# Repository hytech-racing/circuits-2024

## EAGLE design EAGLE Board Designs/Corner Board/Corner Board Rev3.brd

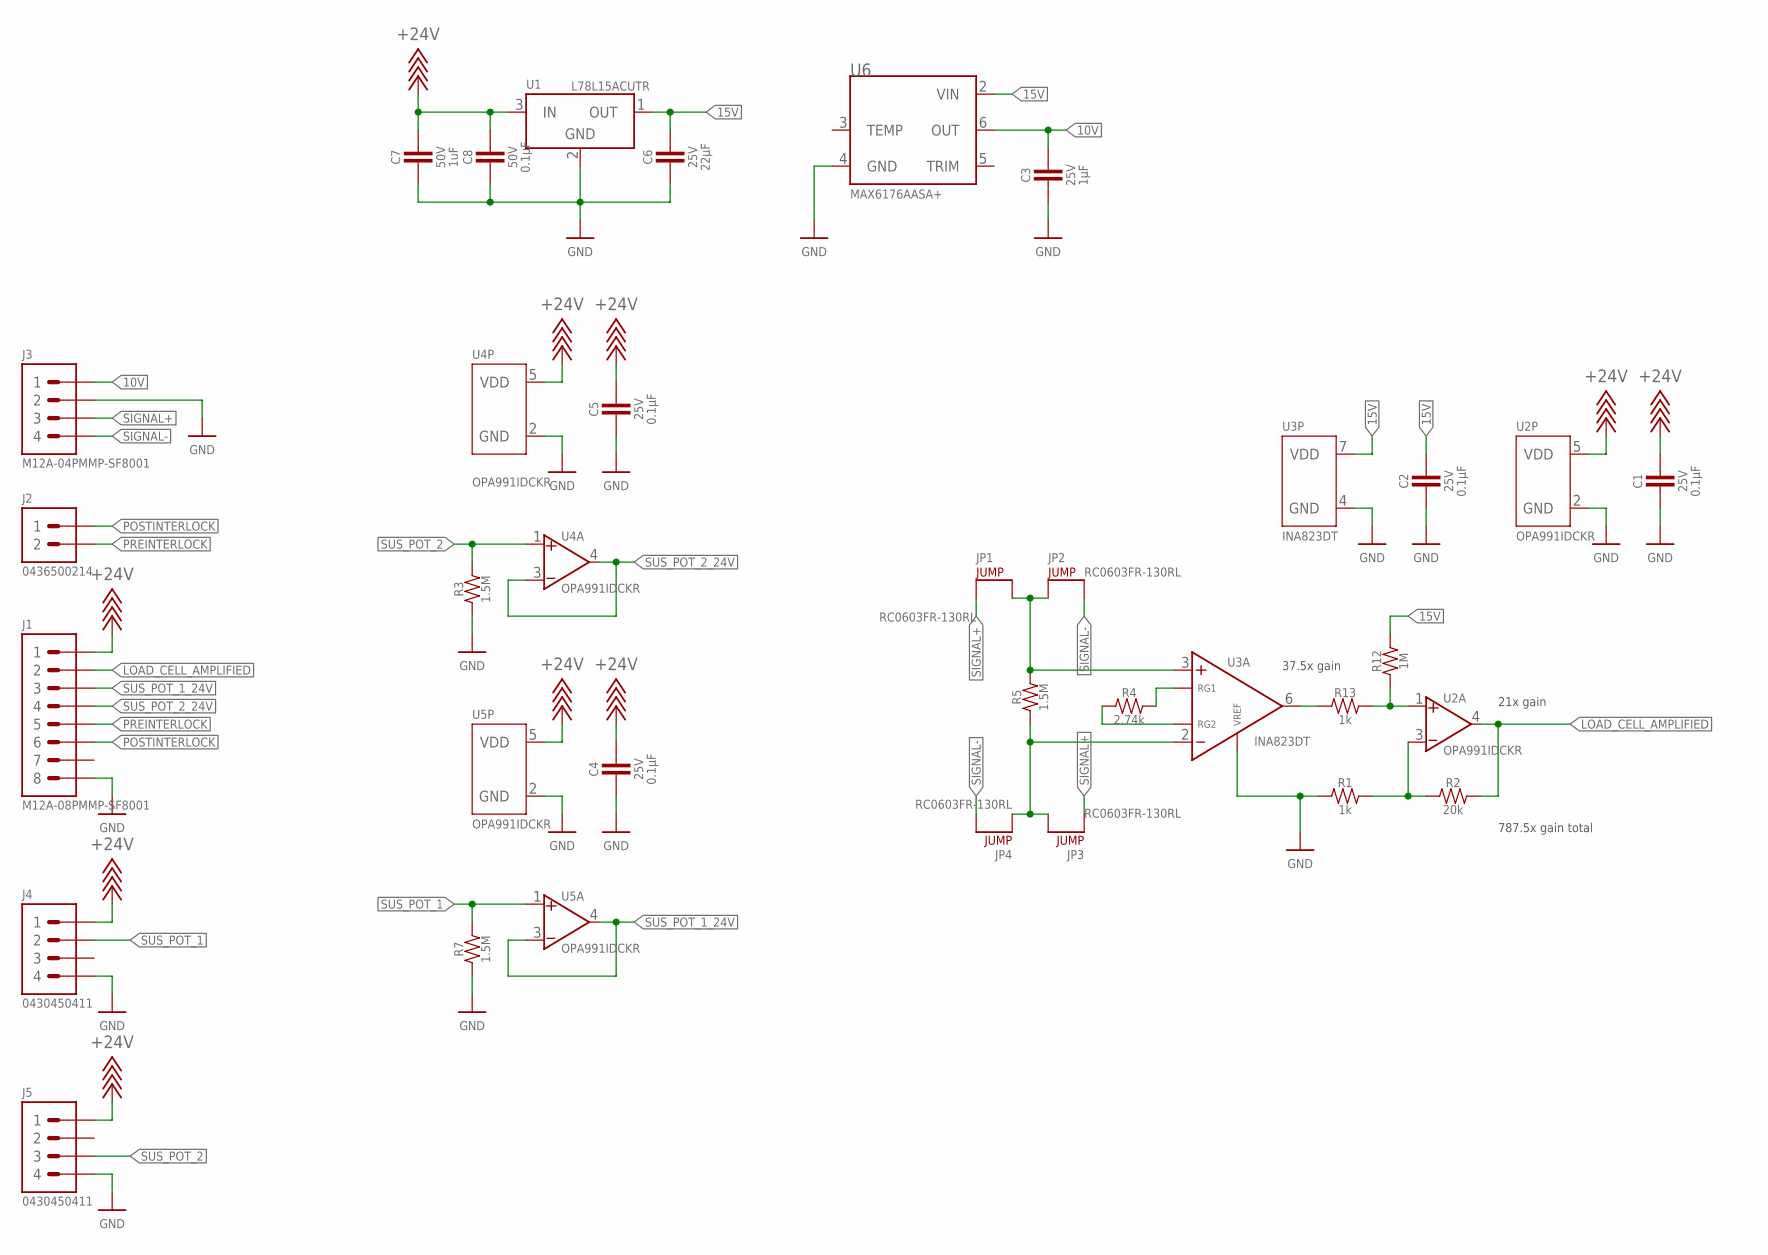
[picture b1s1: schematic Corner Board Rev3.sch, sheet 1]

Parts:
C1, C2, C4, C5: CAPACITOR_0603_25V_0.1UF; 0603-CAP
C3: CAPACITOR_0603_25V_1UF; 0603-CAP
C6: CAPACITOR_0805_25V_22UF; 0805-CAP
C7: CAPACITOR_0603_50V_1UF; 0603-CAP
C8: CAPACITOR_0603_50V_0.1UF; 0603-CAP
J1: CONNECTOR-8_AMPHENOL_M12A_08PMMP_; M12A-08PMMP
J2: CONNECTOR-2_MICROFIT_SMD_RIGHTANGLE_02_SINGLE_BLA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; MOLEX_MICROFIT_SMD_RIGHTANGLE_02_SINGLE
J3: CONNECTOR-4_AMPHENOL_M12A_04PMMP_; M12A-04PMMP
J4, J5: CONNECTOR-4_μF_S_RA_; MOLEX_MICROFIT_SMD_RIGHTANGLE_04_DUAL
JP1, JP2, JP3, JP4: JUMPER_0603_; 0603-RES
R1, R13: RESISTOR_0603_1K; 0603-RES
R2: RESISTOR_0603_20K; 0603-RES
R3, R5, R7: RESISTOR_0603_1.5M; 0603-RES
R4: RESISTOR_0603_2.74K; 0603-RES
R12: RESISTOR_0603_1M; 0603-RES
U1: VOLTAGE_REGULATOR_SOT-89REVERSE_; SOT-89
U2, U4, U5: OPAMP_1_CHANNEL_OPA991; SC-70-5
U3: INA823DT; SOIC-08(NARROW,0.15")
U6: VOLTAGE_REFERENCE_SOIC-8_10V; SOIC-08(NARROW,0.15")

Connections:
10V: C3.1, J3.1, U6.6 (OUT)
15V: C2.1, C6.1, R12.2, U1.1 (OUT), U3.7 (VDD), U6.2 (VIN)
+24V: C1.1, C4.1, C5.1, C7.1, C8.1, J1.1, J4.1, J5.1, U1.3 (IN), U2.5 (VDD), U4.5 (VDD), U5.5 (VDD)
GND: C1.2, C2.2, C3.2, C4.2, C5.2, C6.2, C7.2, C8.2, J1.8, J3.2, J4.4, J5.4, R1.1, R3.1, R7.1, U1.2 (GND), U2.2 (GND), U3.4 (GND), U3.5 (VREF), U4.2 (GND), U5.2 (GND), U6.4 (GND)
LOAD_CELL_AMPLIFIED: J1.2, R2.2, U2.4 (VOUT)
unnamed: R1.2, R2.1, U2.3 (VIN-)
unnamed: R4.2, U3.1 (RG1)
unnamed: R13.1, U3.6 (VOUT)
unnamed: R4.1, U3.8 (RG2)
unnamed: R12.1, R13.2, U2.1 (VIN+)
unnamed: JP3.2, JP4.1, R5.1, U3.2 (VIN-)
unnamed: JP1.2, JP2.1, R5.2, U3.3 (VIN+)
POSTINTERLOCK: J1.6, J2.1
PREINTERLOCK: J1.5, J2.2
SIGNAL+: J3.3, JP1.1, JP3.1
SIGNAL-: J3.4, JP2.2, JP4.2
SUS_POT_1: J4.2, R7.2, U5.1 (VIN+)
SUS_POT_1_24V: J1.3, U5.3 (VIN-), U5.4 (VOUT)
SUS_POT_2: J5.3, R3.2, U4.1 (VIN+)
SUS_POT_2_24V: J1.4, U4.3 (VIN-), U4.4 (VOUT)

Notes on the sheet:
37.5x gain
21x gain
787.5x gain total

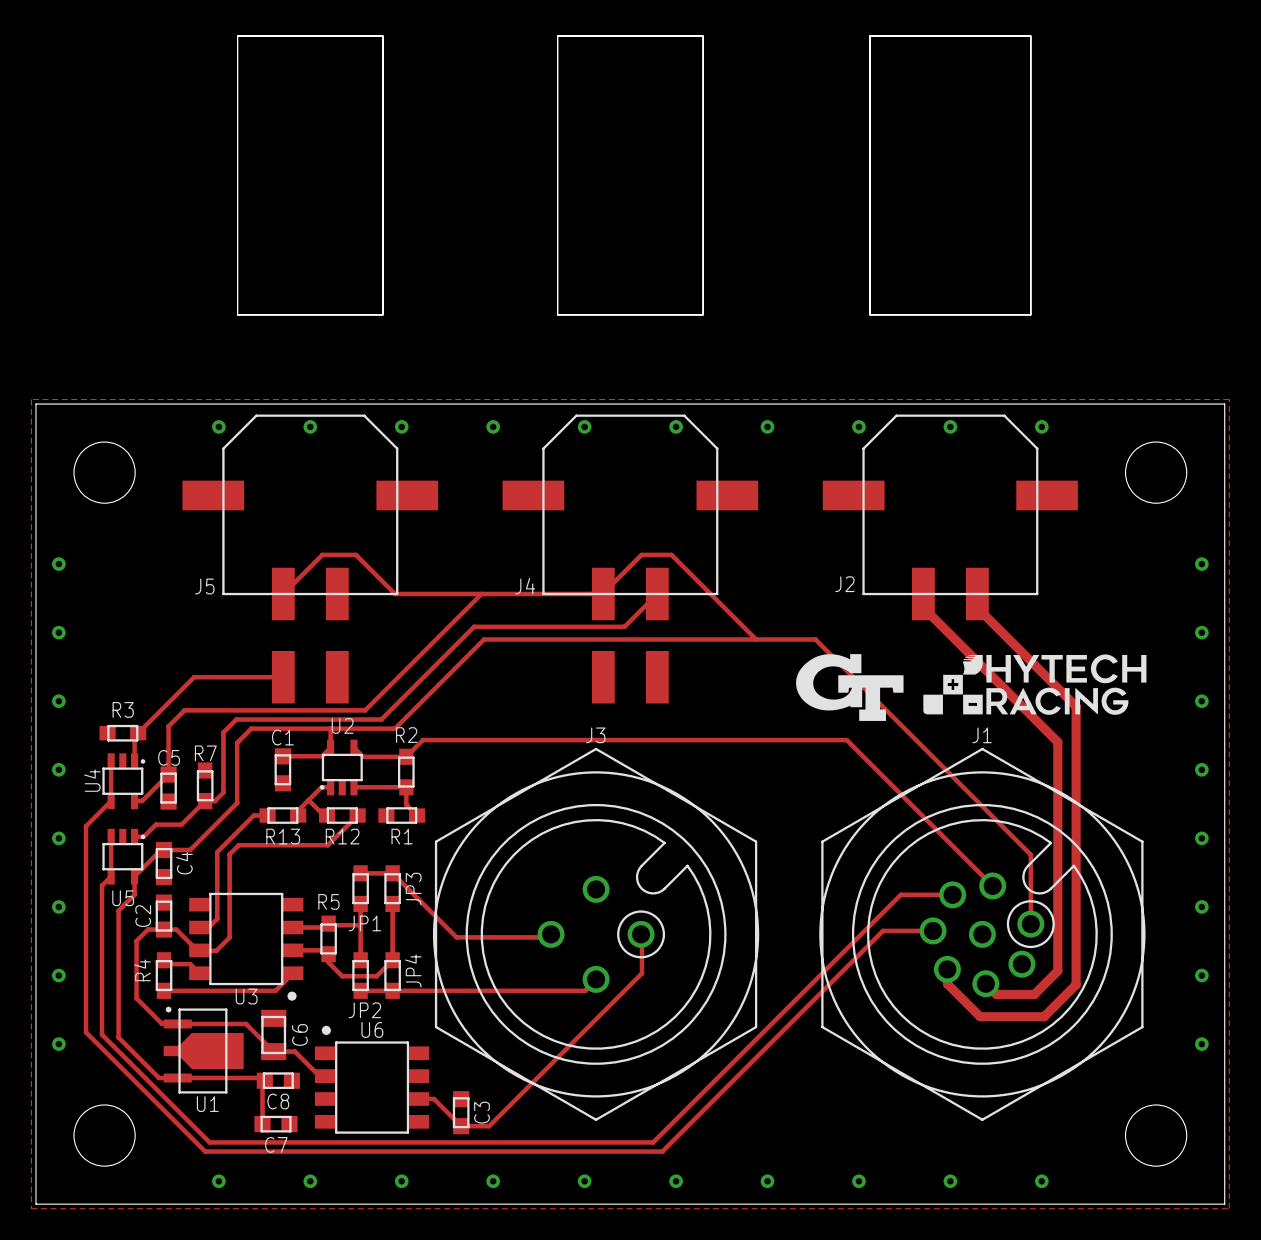
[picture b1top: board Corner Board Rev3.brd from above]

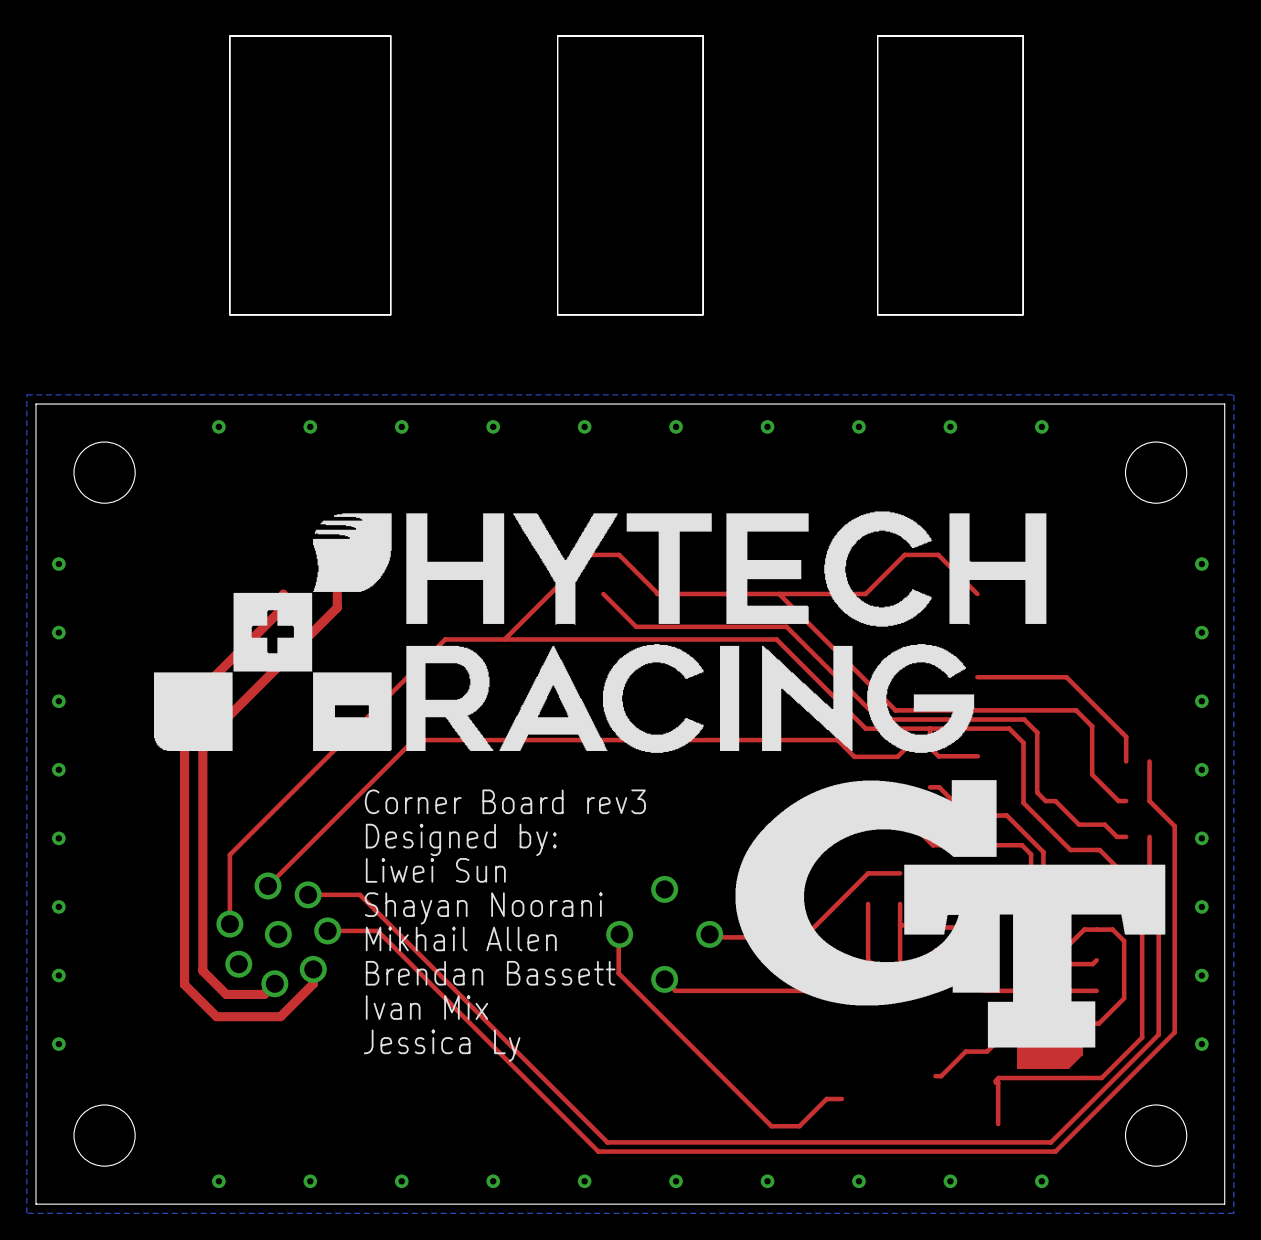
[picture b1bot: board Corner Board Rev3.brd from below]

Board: 2 copper layers, 66.0 x 44.5 mm, 39 parts (2 on the bottom side), 20 nets.

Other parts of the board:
U$6: LOGO_HYTECH_LARGE
U$7, U$8, U$9, U$10: MOUNTING_M3
U$14: LOGO_GT_SMALL
U$15: LOGO_GT_LARGE
U$19: LOGO_HYTECH_SMALL

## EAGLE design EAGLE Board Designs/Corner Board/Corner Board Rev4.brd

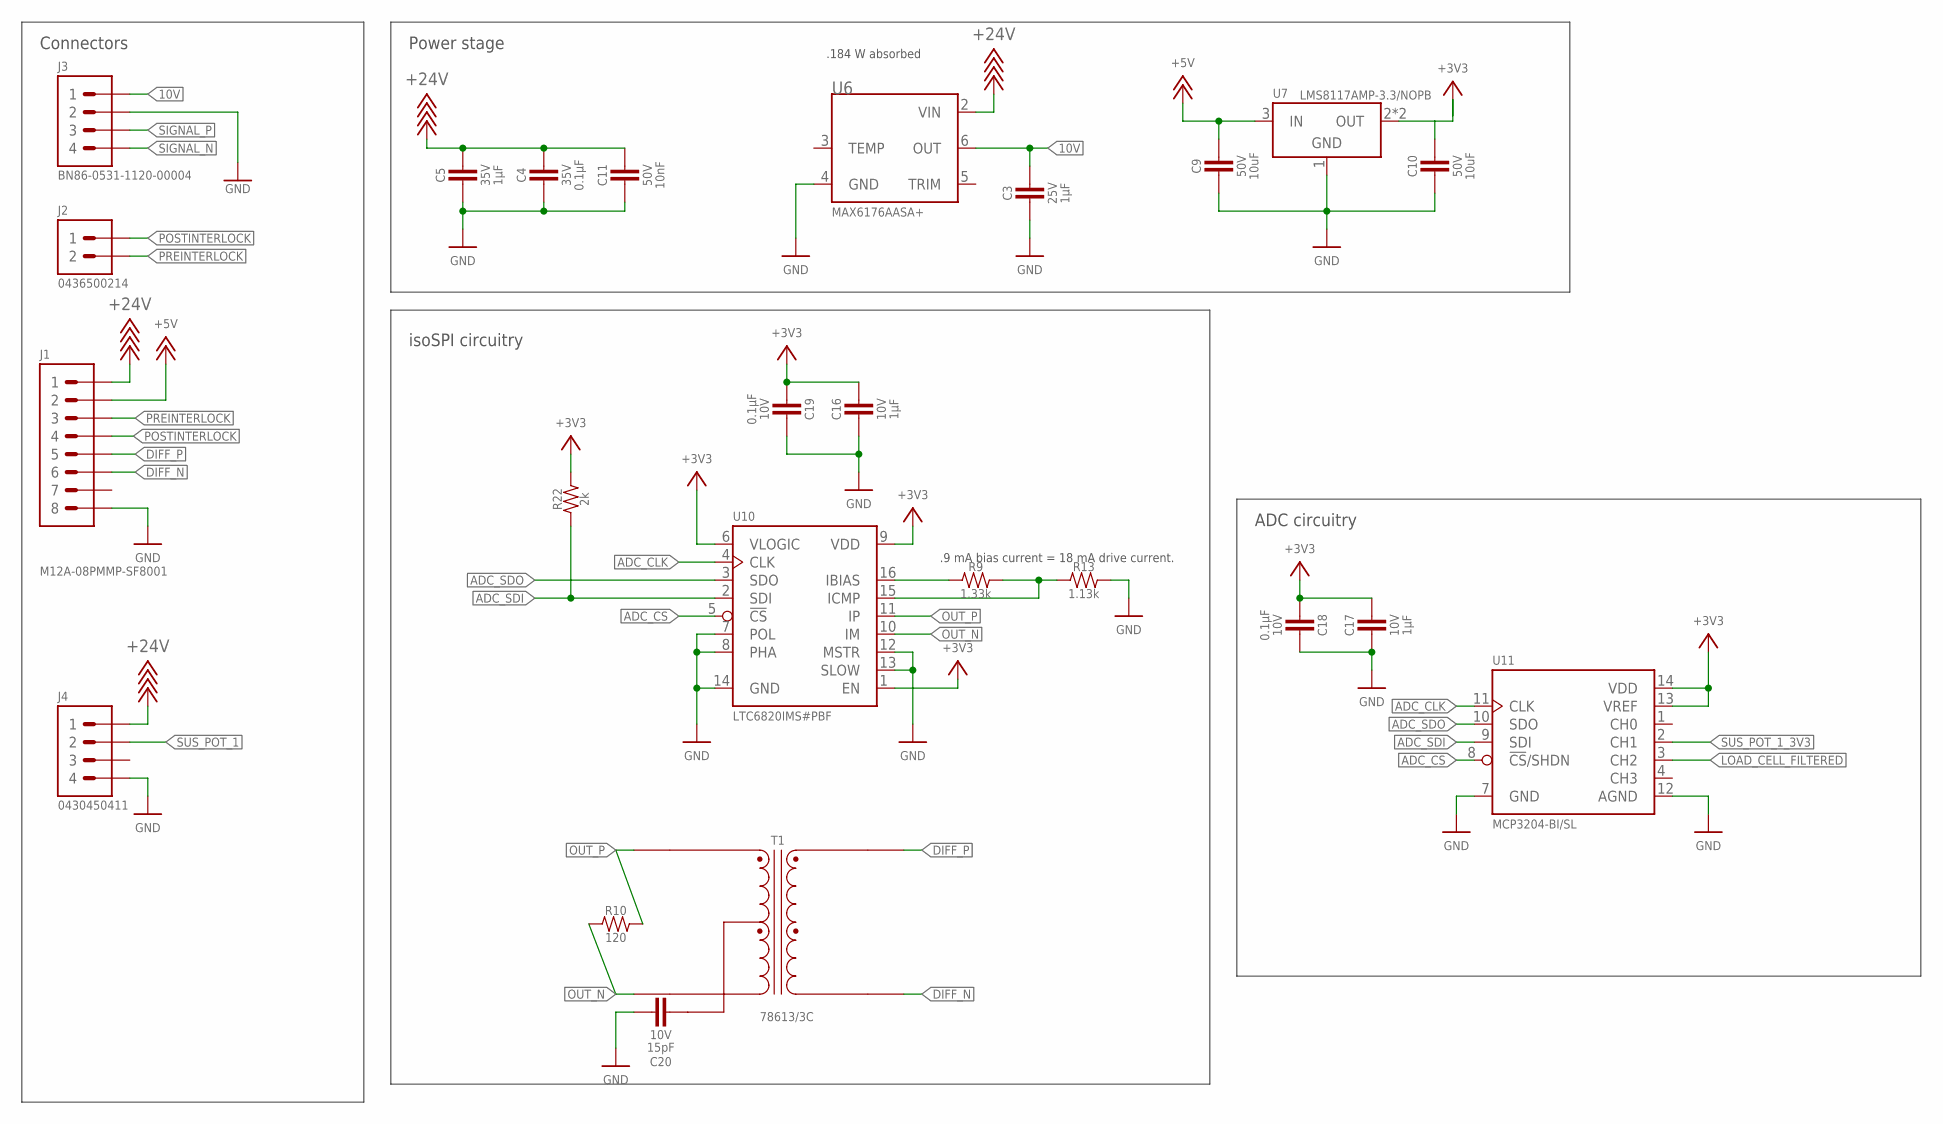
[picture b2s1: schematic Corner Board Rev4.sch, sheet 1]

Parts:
C3: CAPACITOR_0603_25V_1UF; 0603-CAP
C4: CAPACITOR_0603_35V_0.1UF; 0603-CAP
C5: CAPACITOR_0603_35V_1UF; 0603-CAP
C9, C10: CAPACITOR_0805_50V_10UF; 0805-CAP
C11: CAPACITOR_0603_50V_10NF; 0603-CAP
C16, C17: CAPACITOR_0603_10V_1UF; 0603-CAP
C18, C19: CAPACITOR_0603_10V_0.1UF; 0603-CAP
C20: CAPACITOR_0603_10V_15PF; 0603-CAP
J1: CONNECTOR-8_AMPHENOL_M12A_08PMMP_; M12A-08PMMP
J2: CONNECTOR-2_MICROFIT_SMD_RIGHTANGLE_02_SINGLE_BLA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; MOLEX_MICROFIT_SMD_RIGHTANGLE_02_SINGLE
J3: BINDER-M12-A_4_PIN; BINDER-86-0531-1120-00004M12
J4: CONNECTOR-4_μF_S_RA_; MOLEX_MICROFIT_SMD_RIGHTANGLE_04_DUAL
R9: RESISTOR_0603_1.33K; 0603-RES
R10: RESISTOR_0603_120; 0603-RES
R13: RESISTOR_0603_1.13K; 0603-RES
R22: RESISTOR_0603_2K; 0603-RES
T1: 78613/3C_78613/3C_AIRGAP; 78613/3C_AIRGAP
U6: VOLTAGE_REFERENCE_SOIC-8_10V; SOIC-08(NARROW,0.15")
U7: VOLTAGE_REGULATOR_SOT-223_3.3V; SOT-223
U10: LTC6820; MSOP-16
U11: MCP3204; SOIC-14

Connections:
10V: C3.1, J3.1, U6.6 (OUT)
+3V3: C10.1, C16.1, C17.1, C18.2, C19.2, R22.2, U7.2 (OUT), U7.4 (OUT), U10.1 (EN), U10.6 (VLOGIC), U10.9 (VDD), U11.13 (VREF), U11.14 (VDD); also elsewhere on the board
+5V: C9.1, J1.2, U7.3 (IN)
+24V: C4.1, C5.1, C11.1, J1.1, J4.1, U6.2 (VIN); also elsewhere on the board
ADC_CLK: U10.4 (CLK), U11.11 (CLK)
ADC_CS: U10.5 (!CS), U11.8 (!CS!/SHDN)
ADC_SDI: R22.1, U10.2 (SDI), U11.9 (SDI)
ADC_SDO: U10.3 (SDO), U11.10 (SDO)
DIFF_N: J1.6, T1.4 (SEC_1)
DIFF_P: J1.5, T1.6 (SEC_2)
GND: C3.2, C4.2, C5.2, C9.2, C10.2, C11.2, C16.2, C17.2, C18.1, C19.1, C20.2, J1.8, J3.2, J4.4, R13.2, U6.4 (GND), U7.1 (GND), U10.7 (POL), U10.8 (PHA), U10.12 (MSTR), U10.13 (SLOW), U10.14 (GND), U11.7 (GND), U11.12 (AGND); also elsewhere on the board
LOAD_CELL_FILTERED: U11.3 (CH2); also elsewhere on the board
unnamed: C20.1, T1.2 (PRI_CENTER_TAP)
unnamed: R9.1, U10.16 (IBIAS)
unnamed: R9.2, R13.1, U10.15 (ICMP)
OUT_N: R10.1, T1.3 (PRI_2), U10.10 (IM)
OUT_P: R10.2, T1.1 (PRI_1), U10.11 (IP)
POSTINTERLOCK: J1.4, J2.1
PREINTERLOCK: J1.3, J2.2
SIGNAL_N: J3.4; also elsewhere on the board
SIGNAL_P: J3.3; also elsewhere on the board
SUS_POT_1: J4.2; also elsewhere on the board
SUS_POT_1_3V3: U11.2 (CH1); also elsewhere on the board

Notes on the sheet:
.9 mA bias current = 18 mA drive current.
.184 W absorbed
isoSPI circuitry
ADC circuitry
Power stage
Connectors

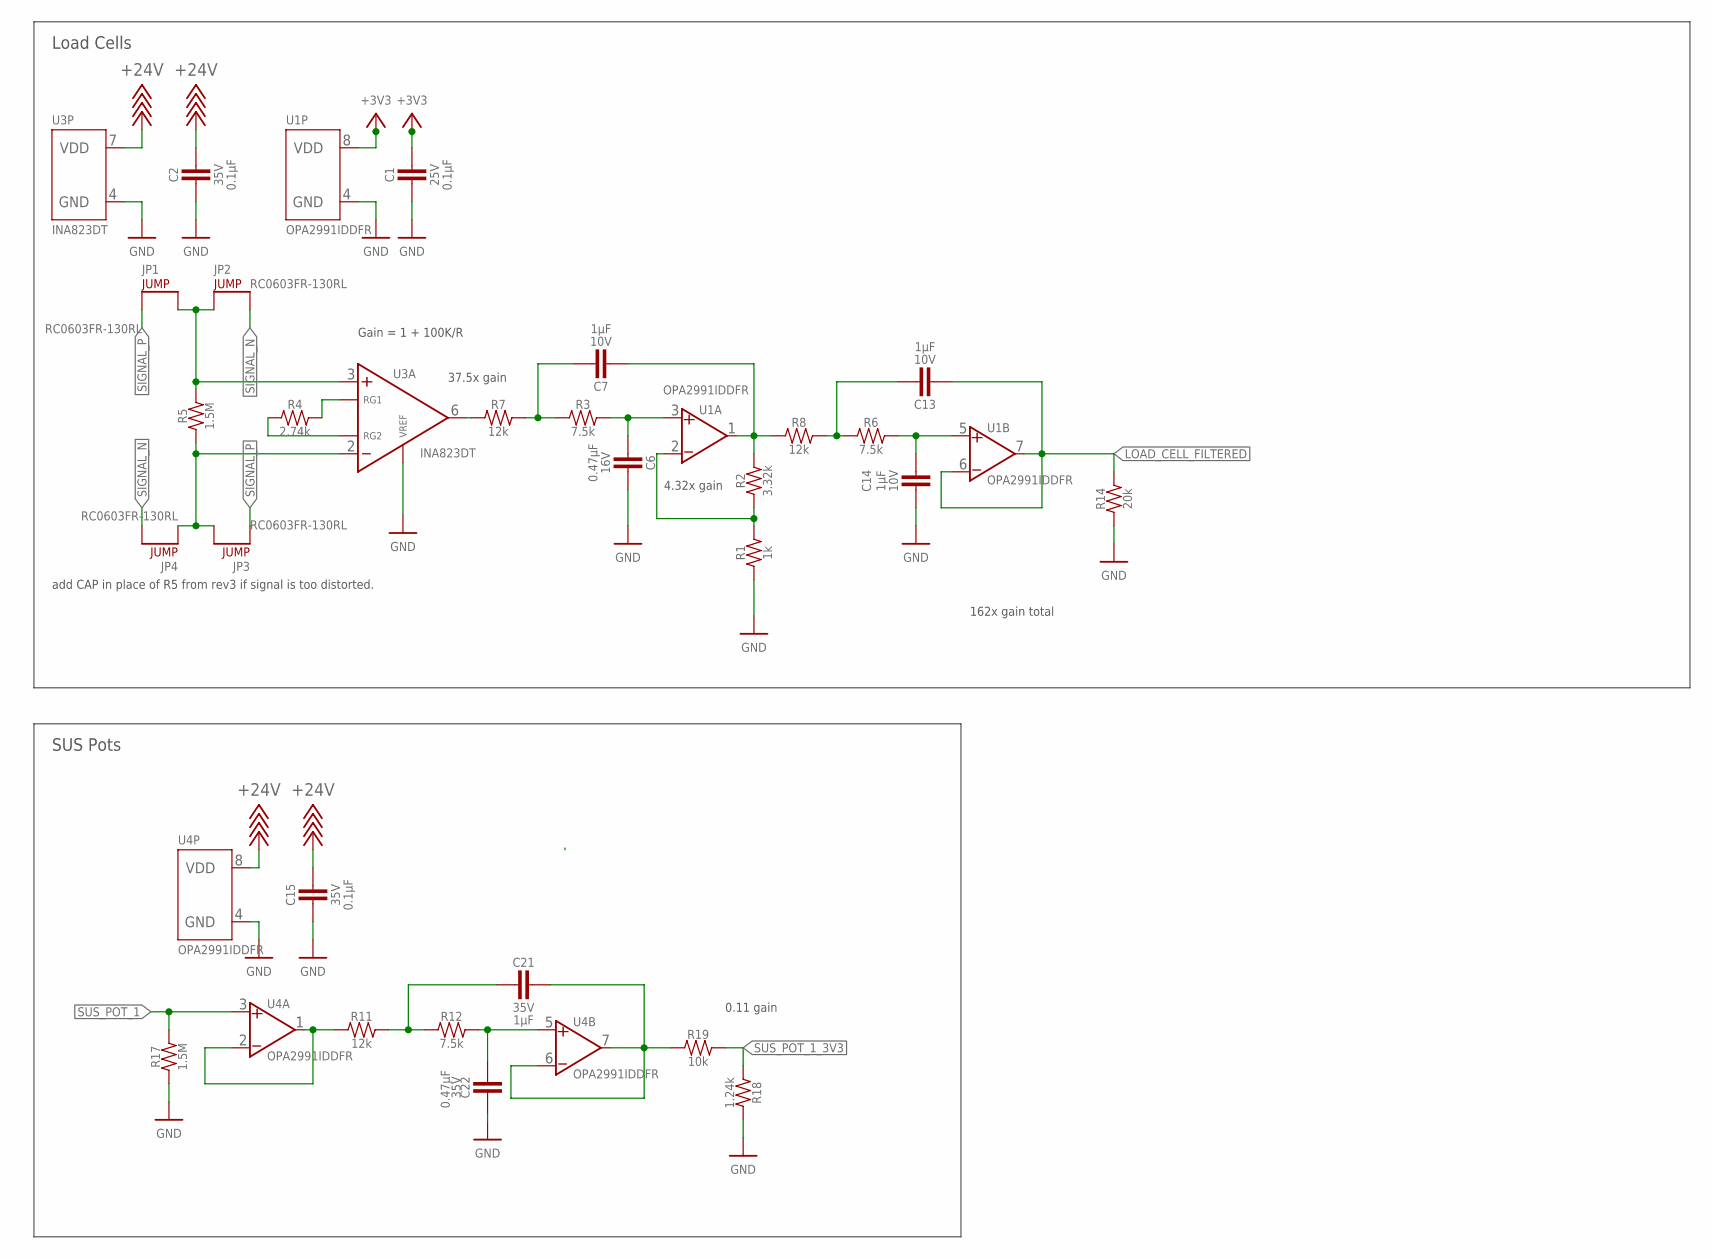
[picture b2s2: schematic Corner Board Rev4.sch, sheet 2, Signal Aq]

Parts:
C1: CAPACITOR_0603_25V_0.1UF; 0603-CAP
C2, C15: CAPACITOR_0603_35V_0.1UF; 0603-CAP
C6: CAPACITOR_0603_16V_0.47UF; 0603-CAP
C7, C13, C14: CAPACITOR_0603_10V_1UF; 0603-CAP
C21: CAPACITOR_0603_35V_1UF; 0603-CAP
C22: CAPACITOR_0603_35V_0.47UF; 0603-CAP
JP1, JP2, JP3, JP4: JUMPER_0603_; 0603-RES
R1: RESISTOR_0603_1K; 0603-RES
R2: RESISTOR_0603_3.32K; 0603-RES
R3, R6, R12: RESISTOR_0603_7.5K; 0603-RES
R4: RESISTOR_0603_2.74K; 0603-RES
R5, R17: RESISTOR_0603_1.5M; 0603-RES
R7, R8, R11: RESISTOR_0603_12K; 0603-RES
R14: RESISTOR_0603_20K; 0603-RES
R18: RESISTOR_0603_1.24K; 0603-RES
R19: RESISTOR_0603_10K; 0603-RES
U1, U4: OPAMP_2_CHANNEL_OPA_2991; SOT-23-8
U3: INA823DT; SOIC-08(NARROW,0.15")

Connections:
+3V3: C1.1, U1.8 (VDD); also elsewhere on the board
+24V: C2.1, C15.1, U3.7 (VDD), U4.8 (VDD); also elsewhere on the board
GND: C1.2, C2.2, C6.1, C14.1, C15.2, C22.2, R1.1, R14.1, R17.1, R18.2, U1.4 (GND), U3.4 (GND), U3.5 (VREF), U4.4 (GND); also elsewhere on the board
LOAD_CELL_AMPLIFIED: C7.2, R2.2, R8.1, U1.1 (VOUT)
LOAD_CELL_FILTERED: C13.2, R14.2, U1.6 (VIN-), U1.7 (VOUT); also elsewhere on the board
LOAD_CELL_POST_INA: R7.1, U3.6 (VOUT)
unnamed: R1.2, R2.1, U1.2 (VIN-)
unnamed: R4.2, U3.1 (RG1)
unnamed: R4.1, U3.8 (RG2)
unnamed: C6.2, R3.2, U1.3 (VIN+)
unnamed 19: JP3.2, JP4.1, R5.1, U3.2 (VIN-); also elsewhere on the board
unnamed: C13.1, R6.1, R8.2
unnamed 21: JP1.2, JP2.1, R5.2, U3.3 (VIN+); also elsewhere on the board
unnamed: C14.2, R6.2, U1.5 (VIN+)
unnamed: C7.1, R3.1, R7.2
unnamed: C21.1, R19.1, U4.6 (VIN-), U4.7 (VOUT)
unnamed: C22.1, R12.2, U4.5 (VIN+)
unnamed: C21.2, R11.2, R12.1
SIGNAL_N: JP2.2, JP4.2; also elsewhere on the board
SIGNAL_P: JP1.1, JP3.1; also elsewhere on the board
SUS_POT_1: R17.2, U4.3 (VIN+); also elsewhere on the board
SUS_POT_1_3V3: R18.1, R19.2; also elsewhere on the board
SUS_POT_1_24V1: R11.1, U4.1 (VOUT), U4.2 (VIN-)

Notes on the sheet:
37.5x gain
4.32x gain
162x gain total
Gain = 1 + 100K/R
0.11 gain
add CAP in place of R5 from rev3 if signal is too distorted.
SUS Pots
Load Cells

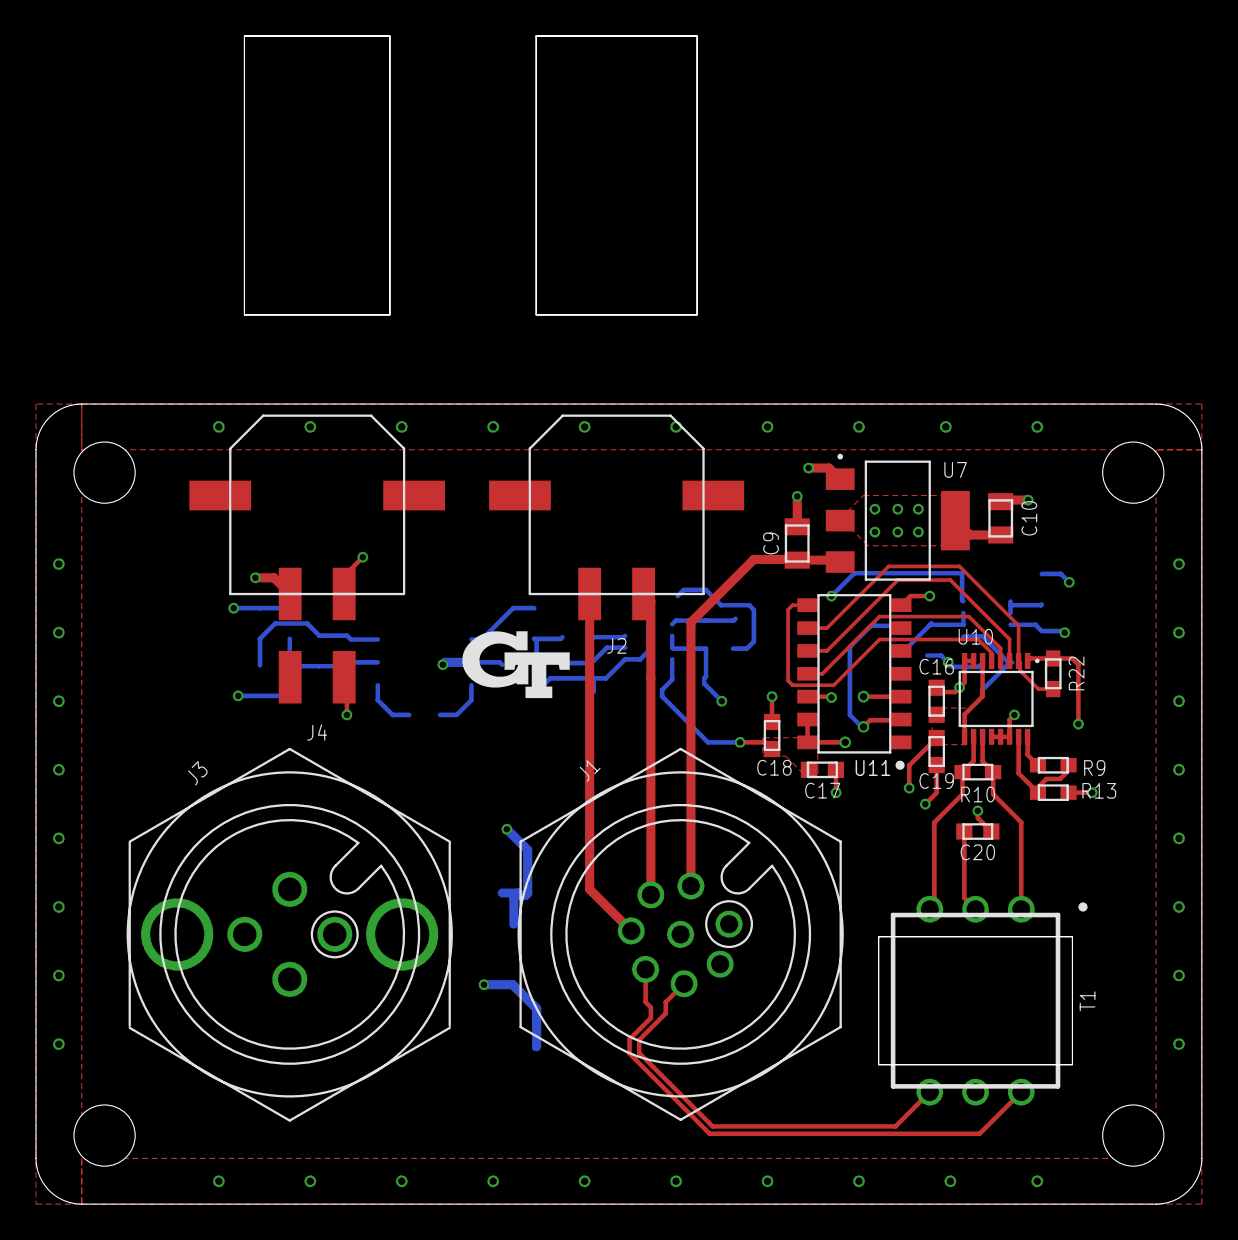
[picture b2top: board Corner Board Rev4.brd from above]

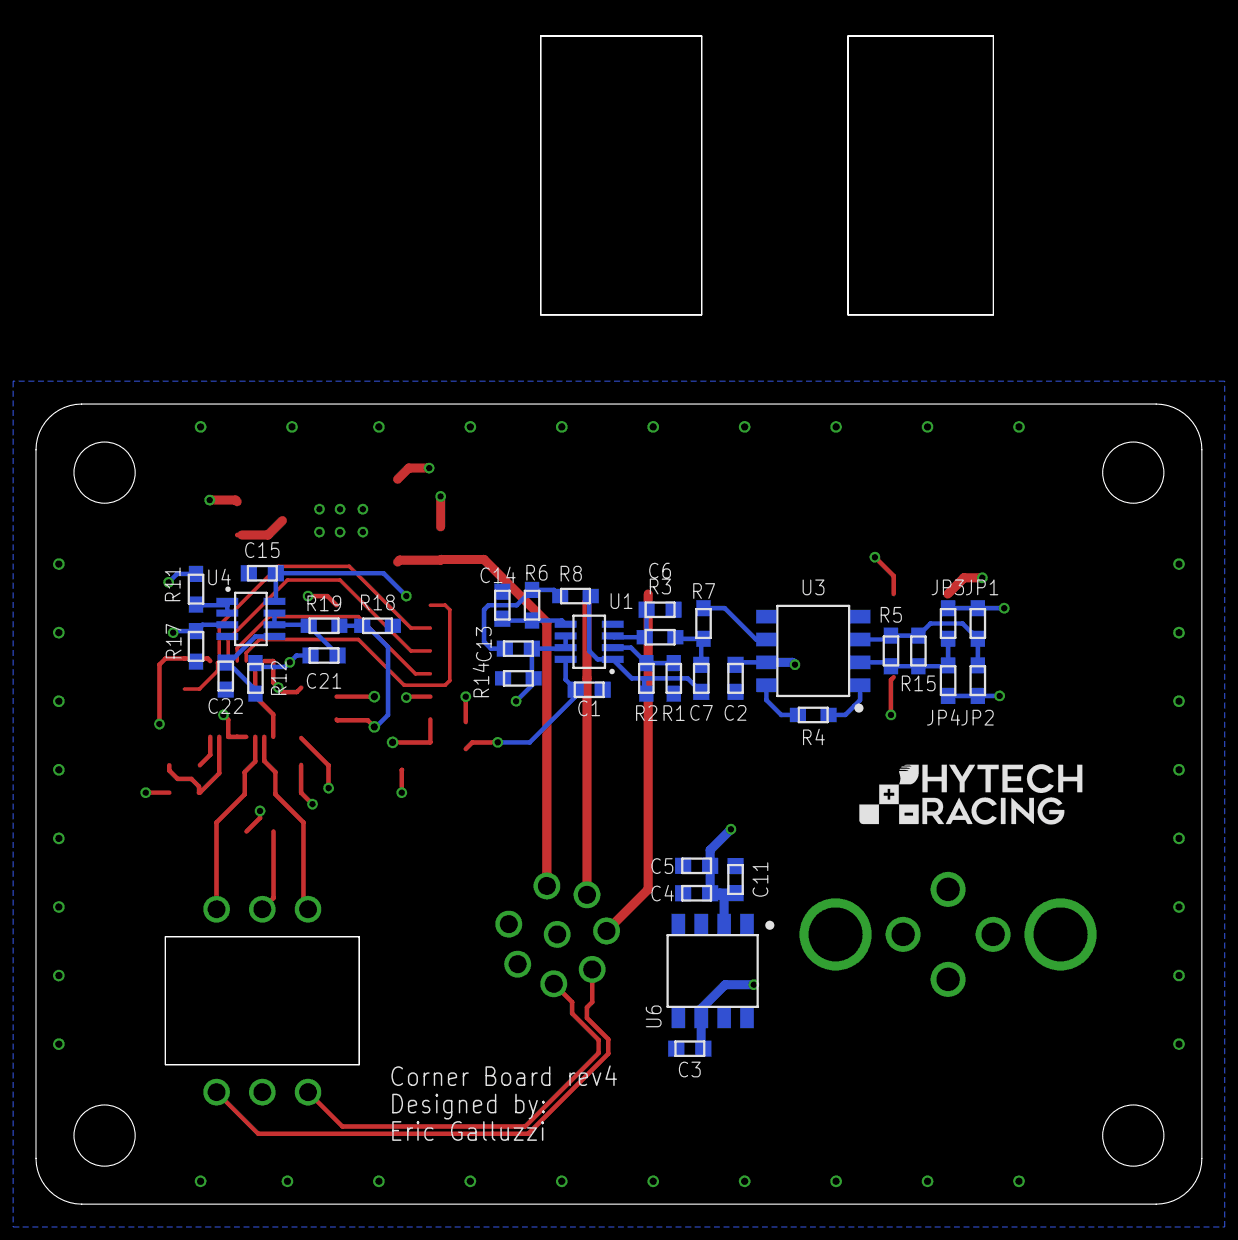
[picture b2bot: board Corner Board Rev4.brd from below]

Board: 4 copper layers, 64.8 x 44.5 mm, 61 parts (37 on the bottom side), 38 nets.

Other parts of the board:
R15: RESISTOR_0603_DNP; 0603-RES
U$1, U$2, U$3, U$7: MOUNTING_M3
U$4: LOGO_HYTECH_SMALL
U$6: LOGO_GT_SMALL

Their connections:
unnamed 19: R15.1; also elsewhere on the board
unnamed 21: R15.2; also elsewhere on the board

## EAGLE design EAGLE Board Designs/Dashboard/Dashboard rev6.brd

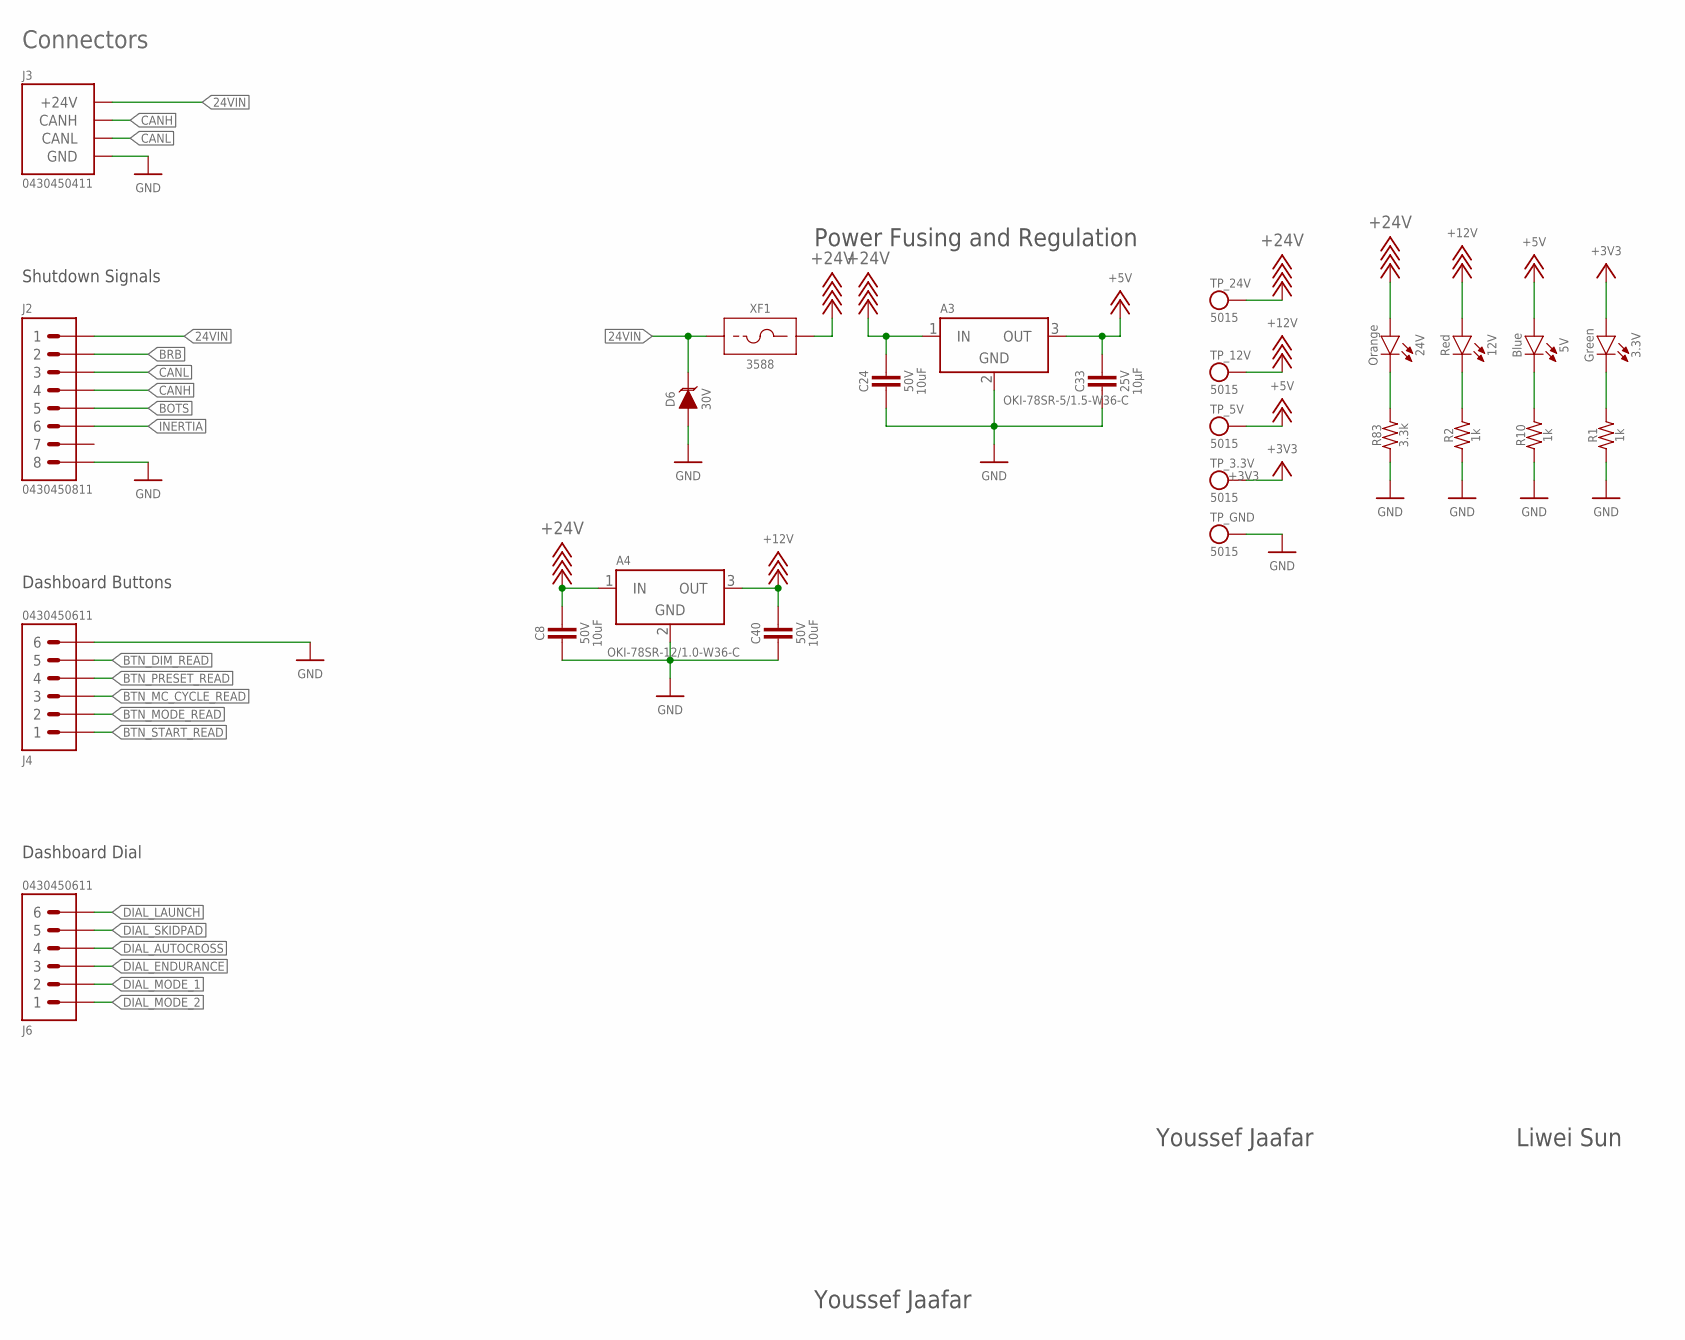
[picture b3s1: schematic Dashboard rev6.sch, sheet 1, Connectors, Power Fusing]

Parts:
3.3V: LED_0603_GREEN; 0603-LED
5V: LED_0603_BLUE; 0603-LED
12V: LED_0603_RED; 0603-LED
24V: LED_0603_ORANGE; 0603-LED
A3: VOLTAGE_REGULATOR_MODULE_OKI-78SR_5V; OKI-78SR
A4: VOLTAGE_REGULATOR_MODULE_OKI-78SR_12V; OKI-78SR
C8, C24, C40: CAPACITOR_0805_50V_10UF; 0805-CAP
C33: CAPACITOR_0603_25V_10UF; 0603-CAP
D6: TVS_DO-214AA_30V; DO-214AA
J2: CONNECTOR-8_μF_S_RA_; MOLEX_MICROFIT_SMD_RIGHTANGLE_08_DUAL
J3: CONNECTOR-CAN_μF_S_RA_; MOLEX_MICROFIT_SMD_RIGHTANGLE_04_DUAL
J4, J6: CONNECTOR-6_μF_S_RA_; MOLEX_MICROFIT_SMD_RIGHTANGLE_06_DUAL
R1, R2, R10: RESISTOR_0603_1K; 0603-RES
R83: RESISTOR_0603_3.3K; 0603-RES
TP_3.3V, TP_5V, TP_12V, TP_24V: TEST_POINT; 5015
TP_GND: TEST_POINT; 5015
XF1: FUSE_HOLDER_MINIBLADESMD; 3588

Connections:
24VIN: D6.2 (C), J2.1, J3.1 (+24V), XF1.1, XF1.2 (1)
+3V3: 3.3V.2 (A), TP_3.3V.1; also elsewhere on the board
+5V: 5V.2 (A), A3.3 (OUT), C33.1, TP_5V.1; also elsewhere on the board
+12V: 12V.2 (A), A4.3 (OUT), C40.1, TP_12V.1; also elsewhere on the board
+24V: 24V.2 (A), A3.1 (IN), A4.1 (IN), C8.1, C24.1, TP_24V.1, XF1.3 (2), XF1.4 (2)
BOTS: J2.5; also elsewhere on the board
BRB: J2.2; also elsewhere on the board
BTN_DIM_READ: J4.5; also elsewhere on the board
BTN_MC_CYCLE_READ: J4.3; also elsewhere on the board
BTN_MODE_READ: J4.2; also elsewhere on the board
BTN_PRESET_READ: J4.4; also elsewhere on the board
BTN_START_READ: J4.1; also elsewhere on the board
CANH: J2.4, J3.4 (CANH); also elsewhere on the board
CANL: J2.3, J3.3 (CANL); also elsewhere on the board
DIAL_AUTOCROSS: J6.4; also elsewhere on the board
DIAL_ENDURANCE: J6.3; also elsewhere on the board
DIAL_LAUNCH: J6.6; also elsewhere on the board
DIAL_MODE_1: J6.2; also elsewhere on the board
DIAL_MODE_2: J6.1; also elsewhere on the board
DIAL_SKIDPAD: J6.5; also elsewhere on the board
GND: A3.2 (GND), A4.2 (GND), C8.2, C24.2, C33.2, C40.2, D6.1 (A), J2.8, J3.2 (GND), J4.6, R1.1, R2.1, R10.1, R83.1, TP_GND.1; also elsewhere on the board
INERTIA: J2.6; also elsewhere on the board
unnamed: 3.3V.1 (C), R1.2
unnamed: 5V.1 (C), R10.2
unnamed: 12V.1 (C), R2.2
unnamed: 24V.1 (C), R83.2

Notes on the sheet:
Power Fusing and Regulation
Connectors
Shutdown Signals
Dashboard Buttons
Dashboard Dial
Youssef Jaafar
Liwei Sun
